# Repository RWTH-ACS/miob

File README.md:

# MIOB - Mobile Input Output Box

<!--  -->
<!--  -->

MIOB, the _Mobile IO Box_ is a flexible unit for interconnecting laboratory equipment and measurements.

Built around a Xilinx Ultrascale+ VC106 FPGA evaluation board, it provides both computation power and IO flexibility for various interfacing tasks in a laboratory.

This repository contains the construction drawings, bill of materials, software and general documentation for building your own MIOB.

## Documentation

- [Xilinx HWserver](./sw/hw_server/README.md)
- [Touchpanel Display](./sw/touchpanel/README.md)
  - [Kiosk Mode](./sw/kiosk/README.md)
- [VILLAScontroller](./sw/villas-controller/README.md)

## Control FPGA Power from Raspberry:

```
#Set pin as output
raspi-gpio set 24 op

#Turn off FPGA Power
raspi-gpio set 24 dh

#Turn on FPGA Power
raspi-gpio set 24 dl
```

## Access Zynq Boot Shell from Raspberry
```
sudo picocom --baud 115200 --flow n /dev/ttyUSB0
```

## Xilinx Vivado Set-up

1. Include all necessary design sources, constraints and simulation sources
    - e.g. for [zcu106_aurora_dino][miob_dino]:
        - [aurora_reset][aurora_reset.vhd]
        - [axi_read_cache][axi_read_cache.vhd]
        - [config_timer][config_timer.vhd]
        - [dinoif_dac][dinoif_dac.vhd]
        - [dinoif_fast_nologic][dinoif_fast_nologic.vhd]
        - [prepend_seqnum][prepend_seqnum.vhd]
        - [registerif][registerif.vhd]
        - [dino-rev-b][dino-rev-b.xdc]

2. If available, execute Tcl file
```
    source <file.tcl>
```

3. Create HDL Wrapper
    - right-click on block design and select "Create HDL Wrapper"

4. Set as Top
    - right-click on wrapped block design and select "Set as Top" 

## Photos

## Authors

- Niklas Eiling ([@n-eiling](https://github.com/n-eiling)), Institute for Automation of Complex Power Systems, RWTH Aachen University)
- Steffen Vogel ([@stv0g](https://github.com/stv0g), Institute for Automation of Complex Power Systems, RWTH Aachen University)

## License

The contents of this repository are licensed under the weakly-reciprocal version of the [CERN Open Hardware Licence Version 2][cern-ohl-v2]

## Funding acknowledment

 The development of [MIOB][miob] has been supported by the following projects:

-  [ERIGrid 2.0][erigrid-2] project of the H2020 Programme under [Grant Agreement No. 870620](https://cordis.europa.eu/project/id/870620)
-  [Urban Energy Lab 4.0][uel] sub-project [InFIS][uel-infis].

[miob]: https://github.com/RWTH-ACS/miob
[uel]: https://www.uel4-0.de/
[uel-infis]: https://www.uel4-0.de/Infrastruktur/Mobiler-Pruefstand/
[erigrid-2]: https://erigrid2.eu
[cern-ohl-v2]: https://ohwr.org/cern_ohl_w_v2.txt
[aurora_reset.vhd]: https://github.com/RWTH-ACS/dino/blob/main/hdl/vivado/design_src/aurora_reset.vhd
[axi_read_cache.vhd]: https://github.com/RWTH-ACS/miob/blob/main/fpga/common/axi_read_cache.vhd
[config_timer.vhd]: https://github.com/RWTH-ACS/dino/blob/main/hdl/vivado/design_src/config_timer.vhd
[dinoif_dac.vhd]: https://github.com/RWTH-ACS/dino/blob/main/hdl/vivado/design_src/dinoif_dac.vhd
[dinoif_fast_nologic.vhd]: https://github.com/RWTH-ACS/dino/blob/main/hdl/vivado/design_src/dinoif_fast_nologic.vhd
[prepend_seqnum.vhd]: https://github.com/RWTH-ACS/dino/blob/main/hdl/vivado/design_src/prepend_seqnum.vhd
[registerif.vhd]: https://github.com/RWTH-ACS/miob/blob/main/fpga/vc707_aurora_xbar/registerif.vhd
[dino-rev-b.xdc]: https://github.com/RWTH-ACS/dino/blob/main/hdl/vivado/constr/dino-rev-b.xdc
[miob_dino]: https://github.com/RWTH-ACS/miob/tree/main/fpga/zcu106_aurora_dino

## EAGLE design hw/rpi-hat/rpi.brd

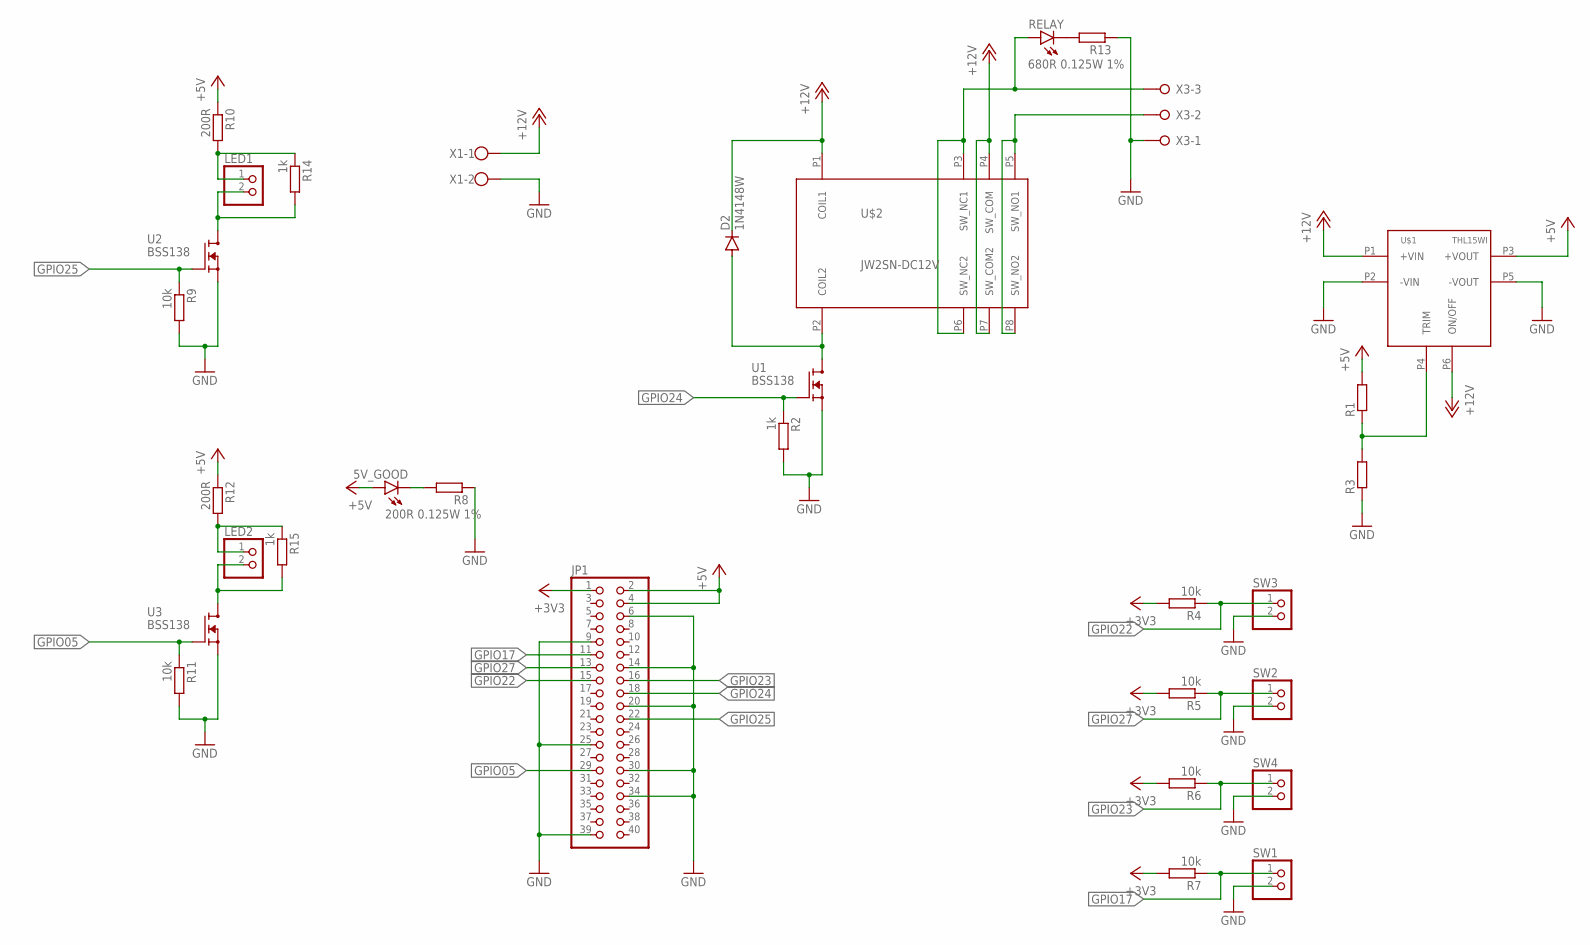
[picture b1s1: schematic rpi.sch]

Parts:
5V_GOOD: LEDCHIPLED_0805; CHIPLED_0805
D2: 1N4148W; SOD-123_MINI-SMA
JP1: PINHD-2X20; 2X20
LED1, LED2: PINHD-1X2; 1X02
R1, R3: R-EU_R0805; R0805
R2, R14, R15: 1k; R0805
R4, R5, R6, R7, R9, R11: 10k; R0805
R8: 200R 0.125W 1%; R0805
R10, R12: 200R; R0805
R13: 680R 0.125W 1%; R0805
RELAY: LEDCHIPLED_0805; CHIPLED_0805
SW1, SW2, SW3, SW4: PINHD-1X2; 1X02
U1, U2, U3: BSS138; SOT23
U$1: THL15WI
U$2: JW2SN-DC12V; JW2FORMC
X1: W237-102
X3: W237-3E

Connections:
12VNC: RELAY.A, U$2.P3 (SW_NC1), U$2.P6 (SW_NC2), X3.3
+3V3: JP1.1, R4.2, R5.2, R6.2, R7.2
+5V: 5V_GOOD.A, JP1.2, JP1.4, R1.2, R10.1, R12.1, U$1.P3 (+VOUT)
+12V: D2.C, U$1.P1 (+VIN), U$1.P6 (ON/OFF), U$2.P1 (COIL1), U$2.P4 (SW_COM), U$2.P7 (SW_COM2), X1.1
GND: JP1.6, JP1.9, JP1.14, JP1.20, JP1.25, JP1.30, JP1.34, JP1.39, R2.2, R3.1, R8.1, R9.2, R11.2, R13.1, SW1.2, SW2.2, SW3.2, SW4.2, U1.2 (S), U2.2 (S), U3.2 (S), U$1.P2 (-VIN), U$1.P5 (-VOUT), X1.2, X3.1
GPIO05: JP1.29, R11.1, U3.1 (G)
GPIO17: JP1.11, R7.1, SW1.1
GPIO22: JP1.15, R4.1, SW3.1
GPIO23: JP1.16, R6.1, SW4.1
GPIO24: JP1.18, R2.1, U1.1 (G)
GPIO25: JP1.22, R9.1, U2.1 (G)
GPIO27: JP1.13, R5.1, SW2.1
unnamed: R1.1, R3.2, U$1.P4 (TRIM)
unnamed: D2.A, U1.3 (D), U$2.P2 (COIL2)
unnamed: LED1.2, R14.2, U2.3 (D)
unnamed: U$2.P5 (SW_NO1), U$2.P8 (SW_NO2), X3.2
unnamed: 5V_GOOD.C, R8.2
unnamed: LED1.1, R10.2, R14.1
unnamed: LED2.2, R15.2, U3.3 (D)
unnamed: LED2.1, R12.2, R15.1
unnamed: R13.2, RELAY.C

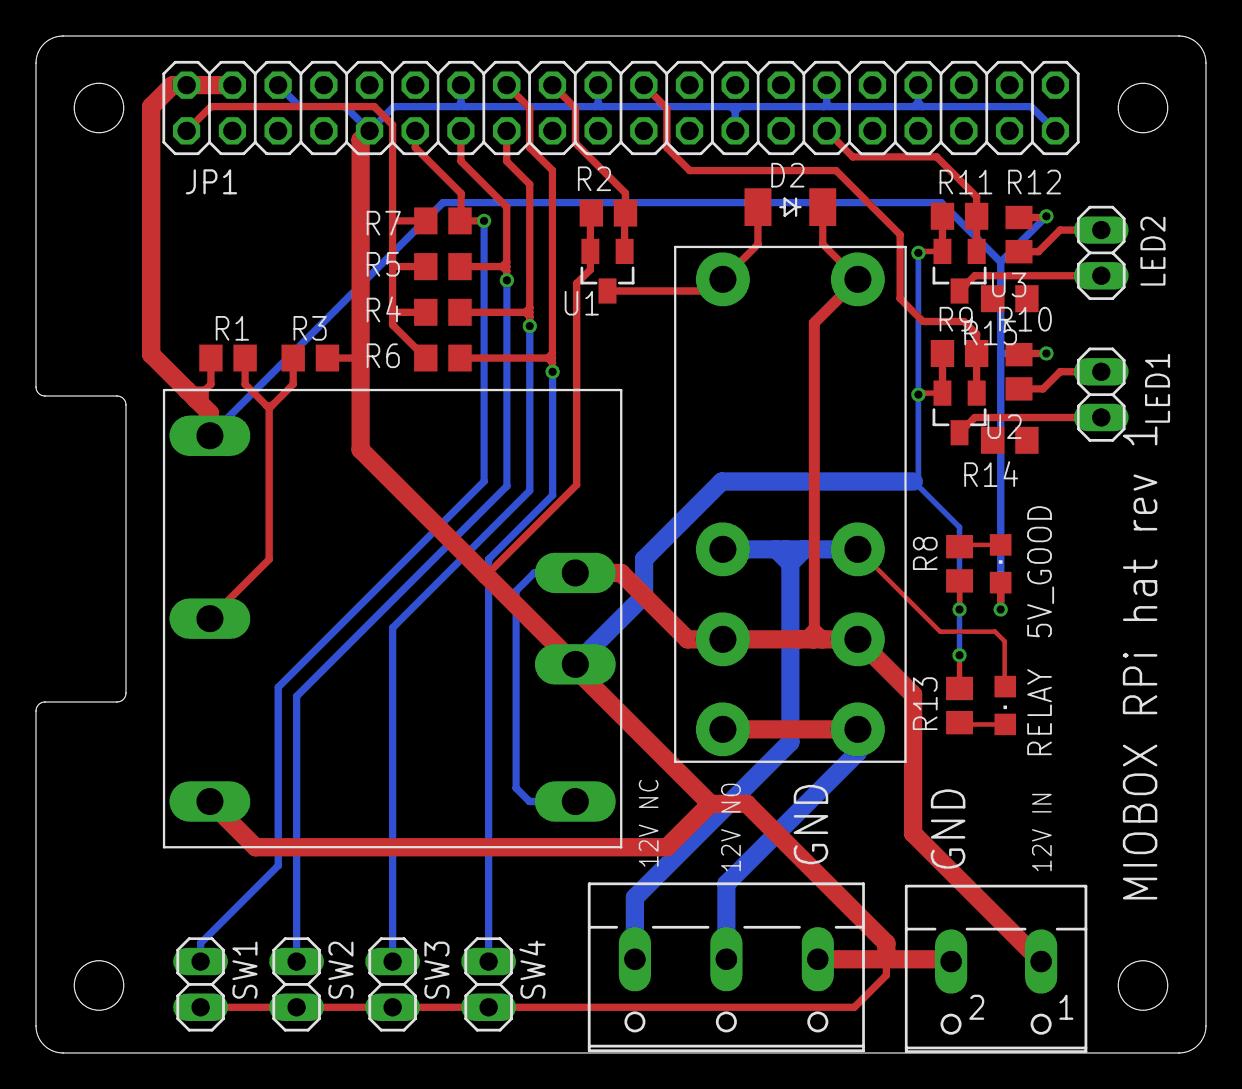
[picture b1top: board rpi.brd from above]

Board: 2 copper layers, 65.0 x 56.5 mm, 32 parts (0 on the bottom side), 21 nets.

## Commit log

2022-02-07 add initial hw design
2022-02-07 add raspberry hat pcb design
2022-02-07 add frontpanel design
2022-02-07 use correct license
2022-02-07 updated BOM
2022-02-11 rpi hat: fix wrong hole size for dcdc converter
2022-02-11 rpi hat: fix a few traces being to close to vias
2022-02-11 rpi hat: fix more traces being to close to vias
2022-02-24 hw/rpi-ha: add bleeder resistors for external LEDs
2022-02-25 hw/frontpanel: add cutouts for LEDs, add step file
2022-02-25 hw/frontpanel: fix step file and add dxf file
2022-03-24 sw: add systemd file to autostart qemu x86 docker interpreter
2022-03-24 sw: mention enabling the systemd service and fix service file
2022-03-24 update BOM
2022-03-24 add some docs for display and hw_server
2022-03-24 add link to systemd unit
2022-03-24 hw/frontpanel: add 3d model for filler
2022-03-24 hw/frontpanel/fillers: make backplate thinner, add filler for single row sfp module
2022-03-24 fpga: add zcu106_aurora_minimal example
2022-03-25 add instructions for kiosk mode
2022-03-25 document setup of VILLAScontroller
2022-03-25 add photos
2022-03-25 restructure docs
2022-03-25 sw: add snmp config
2022-03-25 fpga: add passthrough example
2022-03-25 add manual for bringing up new miob raspberrys
2022-03-25 fpga/zcu106_aurora_passthrough: add bitstream
2022-03-30 fpga/zcu106_aurora_passthrough: update README.md
2022-03-30 fpga/vc707_aurora_passthrough: add design for passthrough on the vc707 platform
2022-03-31 fpga/vc707_aurora_passthrough: set frequency config via FPGA pins
2022-03-31 fpga/vc707_aurora_passthrough: add bistream
2022-03-31 fpga: add more details to READMEs
2022-03-31 fpga/vc707_aurora_passthrough: remove axi clock converters thereby simplifying the design
2022-03-31 hw/frontpanel: add empty filler for prototype
2022-04-04 fpga/vc707_aurora_xbar: add project for xbar design
2022-04-04 fpga/vc707_aurora_xbar: add channes 2 and 3
2022-04-04 fpga/vc707_aurora_xbar: add xbar to design and demo IP that configures the crossbar
2022-04-06 fpga/vc707_aurora_xbar: verify design and test with real hardware
    add a testbench xbar_config_demo_tb.vhd
    add verified bitstreams
2022-04-09 fpga: change vc707_aurora_xbar and zcu106_aurora_minimal designs to use 32 bit lande width
2022-04-29 add xsdb script to program fpga
2022-04-29 update systemd service files and fpga tcl script
2022-05-10 fpga: fix RTDS desynchronization
    fpga/vc707_aurora_xbar: remove CRCs in the Aurora IP for all but
    channel0. OPAL-RT requires CRCs but RTDS requires no CRCs.
    Add IP to add padding and remove the last word of an AXI stream frame
    fpga/vc707_aurora_passthrough: remove CRCs
2022-05-17 fpga/vc707_pcie_minimal: add a minimal PCIe design for the vc707
2022-06-01 Added Programming Guide for Cortex R
2022-06-02 hw/rpi-hat: add rev 2 of rpi hat
2022-06-02 fpga/vc707_aurora_xbar: add first draf for including pcie connection
2022-06-02 docs: make cortex-r programming guide a bit more verbose
2022-08-30 fpga/vc707_aurora_xbar: add interrupt controller from villasfpga repository to create PCIE MSI interrupts
2022-08-31 miob/fpga: add zcu106 smmu project based on xilinx example
2022-08-31 gitignore: do not ignore vivado IP configs
2022-09-02 sw/yocto: add yocto layer meta-miob for building yocto for the miob hardware platform
2022-09-05 sw/yocto: add machine miob-zcu106-zynqmp and hwdef for smmu example
2022-09-05 sw/yocto: add device tree additions and kernel config
2022-09-06 sw/yocto: add miob-dev-image that installs some useful packages on top of petalinux-image-minimal
2022-09-06 sw: move rpi sw to sw/rpi
2022-09-06 sw/yocto: add package manager, remove docker
2022-09-06 sw/yocto remove reference to nonexisting docker variable
2022-09-06 sw/yocto: add patch for nspr to correctly build with extended buildtools
2022-09-09 sw/yocto: make smmu work
2022-09-12 sw/yocto: add SMMU register init; add dhcpcd config; add vfiotest
2022-09-12 sw/yocto: add peekpoke
2022-09-14 sw/yocto: change hardware and smmu settings to use DMA with scatter-gather. This makes vfiotest not work anymore because sg requires different register settings
2022-10-04 sw/yocto: add meta-villasnode layer
2022-10-26 sw/yocto: add zcu106 base device tree to miob image so i2c busses are correctly detected by linux
2022-10-26 sw/yocto: fix address of package repos
2022-11-03 sw/yocto: add frutools recipe
2022-11-03 sw/yocto: add cern-ipmi recipe to meta-miob layer
2022-11-03 sw/yocto: fix issues with fmc eeprom tools, add deploy script for package repo
2022-11-29 interfaces: add aurora interface for RTDS and OPAL-RT including example models and bitstreams
2022-11-29 fpga/zcu106_smmu: improve smmus design
2022-11-29 fpga/vc707_aurora_xbar: fix xbar_config_demo
2022-11-29 sw/yocto: add license and copyright note
2022-11-29 fpga/vc707_aurora_xbar: update bitstream and debug probes
2022-12-02 README: add FPGA powercontrol documentation
2022-12-02 README: add documentation for how to access FPGA shell
2022-12-08 sw/yocto/meta-miob: update Xilinx HW and device tree modifications to latest dino design
2023-07-28 sw/yocto: fix fmceeprom recipe
2023-07-28 add more minimal bitstream and change device-tree accordingly. This fixes that the axis switch didn't show up in the linux devices
2023-10-16 yocto: add clang to image
2023-10-16 yocto: set SFP clock to 250Mhz
2024-02-08 fpga/vc707_aurora_xbar_new: update design to include dino
2024-02-08 fpga/zcu106_aurora_minimal: update design
2024-02-08 fpga/zcu106_smmu: update design
2024-04-18 fpga: add tcl script to generate board design for vc707_aurora_xbar
2024-04-18 fpga: update vhdl
2024-05-03 fpga: add tcl export for vc707_aurora_xbar
2024-05-03 fpga: add vivado archive for vc707_aurora_xbar
2024-09-19 fpga: add zcu106_aurora_dino
2024-10-02 WIP: add Vivado set-up instructions
2024-10-29 fix formatting
2024-11-15 yocto: update yocto recipes with latest changes from bitstream
2025-01-24 update vivado files
